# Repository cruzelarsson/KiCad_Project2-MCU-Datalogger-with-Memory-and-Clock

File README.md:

MCU Datalogger with memory and clock 

• Designed and debugged multi-layer PCB design using microcontroller, EEPROM, and RTC module with a regulated power supply, improving thermal performance ~30% by utilizing accurate design & routing methodologies ensuring zero DRC & ERC errors.

• Evaluated electrical and firmware-level interactions between MCU and peripherals for stable operation.

• Validated MCU communication protocols using I2C for peripheral data exchange.

•	Produced a compact design with status LEDs, mounting holes and modular connectors, ensuring physical durability and visible feedback. 

-------------------------------------------------------------------------------------------------------------------------------------------------------
This project — MCU Datalogger with Memory and Clock — was supported by PCBWay through their PCB prototyping sponsorship program.

PCBWay provided high-quality manufactured boards that arrived perfectly aligned and finished. The fabrication quality was excellent, with sharp silkscreen printing, clean solder masks, and precise drill accuracy.

A huge thanks to PCBWay for their support in helping bring this project to life. Their fast turnaround and reliable service made the prototyping process straightforward and efficient.

Below you will find the printed out board; the missing components will be added and uploaded soon. Thank you!

-------------------------------------------------------------------------------------------------------------------------------------------------------
3D layout of 2 layer PCB (final design)

-------------------------------------------------------------------------------------------------------------------------------------------------------

PCB Board layout with board specifications 

-------------------------------------------------------------------------------------------------------------------------------------------------------

Schematic Editor Layout of MCU Datalogger

-------------------------------------------------------------------------------------------------------------------------------------------------------

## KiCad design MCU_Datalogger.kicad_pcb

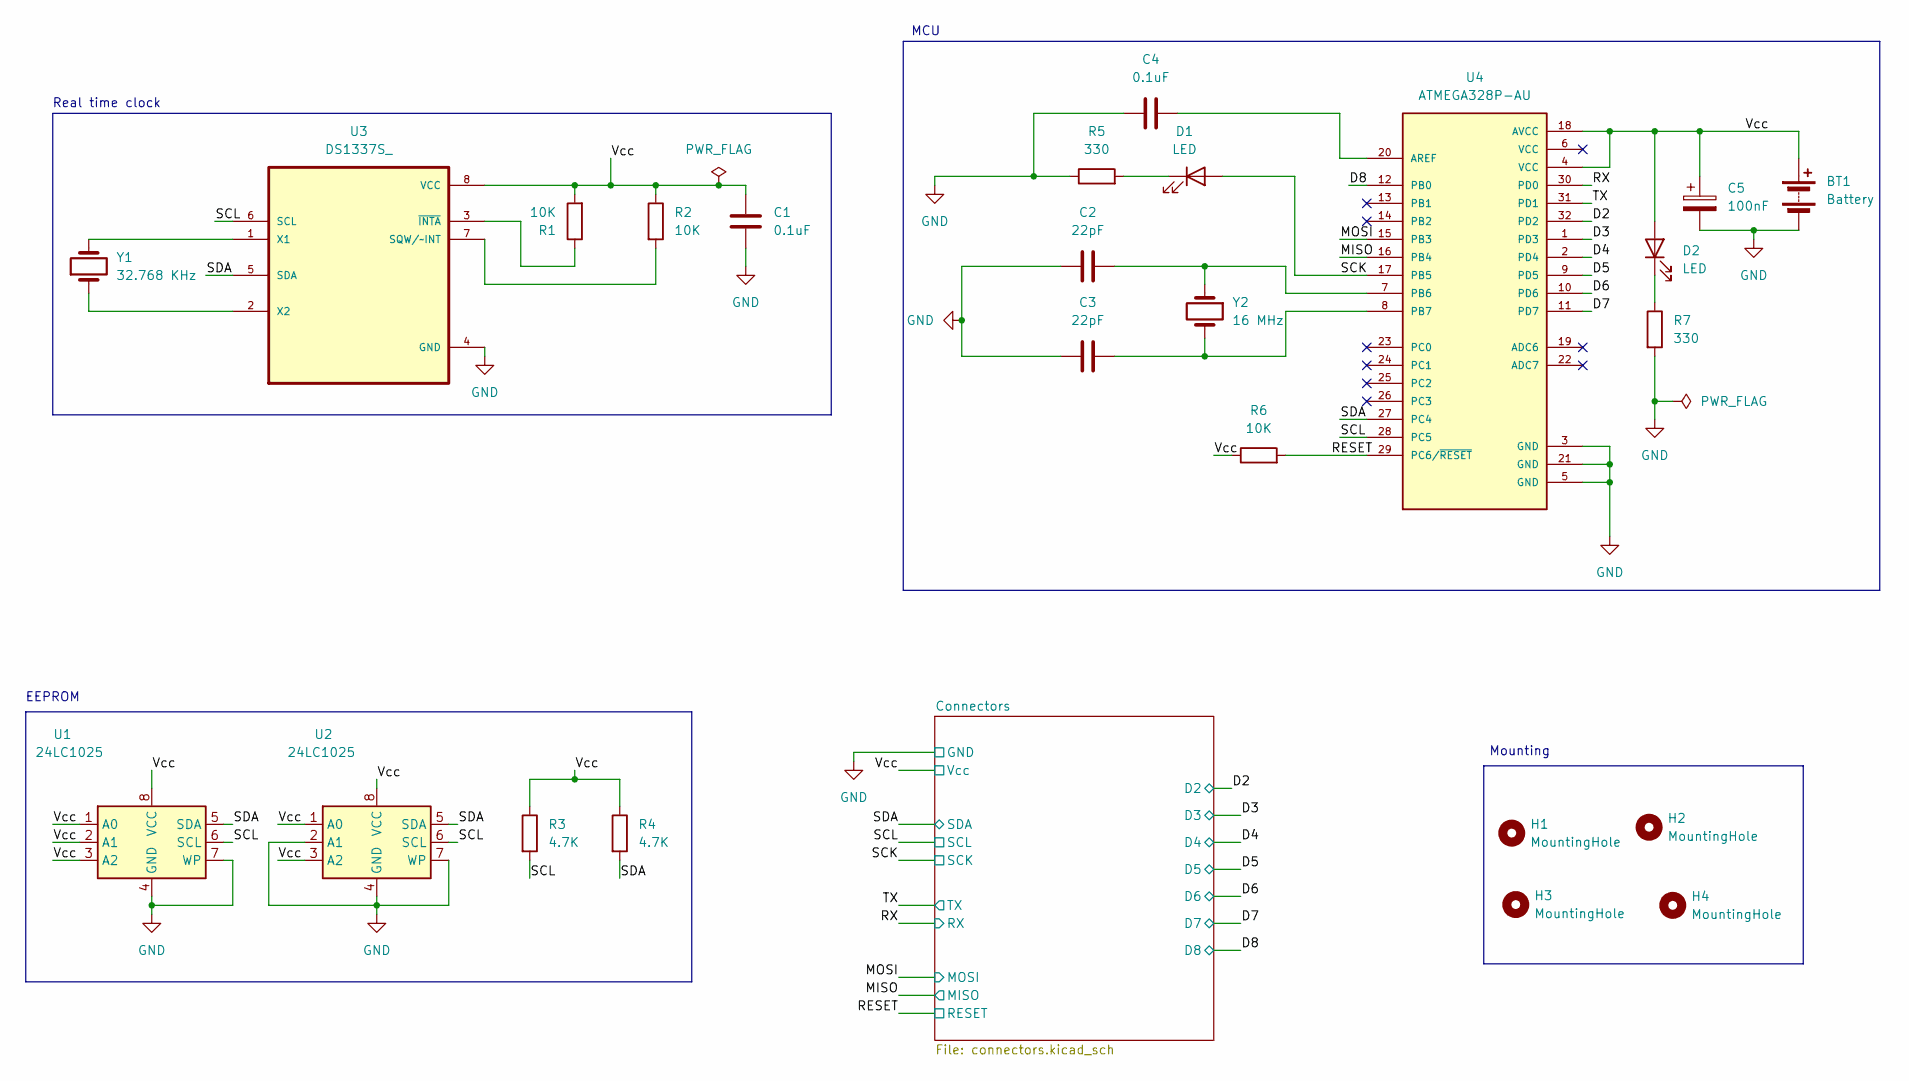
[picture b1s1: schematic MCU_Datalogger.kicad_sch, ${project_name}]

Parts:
BT1: Battery; PinHeader_1x02_P2.54mm_Vertical
C1, C4: 0.1uF; C_0805_2012Metric
C2, C3: 22pF; C_0805_2012Metric
C5: 100nF; C_0805_2012Metric
D1, D2: LED; LED_0805_2012Metric
H1, H2, H3, H4: MountingHole; MountingHole_2.1mm
R1, R2, R6: 10K; R_0805_2012Metric
R3, R4: 4.7K; R_0805_2012Metric
R5, R7: 330; R_0805_2012Metric
U1, U2: 24LC1025; SOIC-8_5.3x5.3mm_P1.27mm
U3: DS1337S_; SOIC127P600X175-8N
U4: ATMEGA328P-AU; QFP80P900X900X120-32N; PARTREV 8271A
Y1: 32.768 KHz; Crystal_SMD_5032-2Pin_5.0x3.2mm_HandSoldering
Y2: 16 MHz; Crystal_SMD_5032-2Pin_5.0x3.2mm_HandSoldering

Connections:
/D2: U4.32 (PD2); also elsewhere on the board
/D3: U4.1 (PD3); also elsewhere on the board
/D4: U4.2 (PD4); also elsewhere on the board
/D5: U4.9 (PD5); also elsewhere on the board
/D6: U4.10 (PD6); also elsewhere on the board
/D7: U4.11 (PD7); also elsewhere on the board
/D8: U4.12 (PB0); also elsewhere on the board
/MISO: U4.16 (PB4); also elsewhere on the board
/MOSI: U4.15 (PB3); also elsewhere on the board
/RESET: R6.2, U4.29 (PC6/~RESET); also elsewhere on the board
/RX: U4.30 (PD0); also elsewhere on the board
/SCK: D1.2 (A), U4.17 (PB5); also elsewhere on the board
/SCL: R3.2, U1.6 (SCL), U2.6 (SCL), U3.6 (SCL), U4.28 (PC5); also elsewhere on the board
/SDA: R4.2, U1.5 (SDA), U2.5 (SDA), U3.5 (SDA), U4.27 (PC4); also elsewhere on the board
/TX: U4.31 (PD1); also elsewhere on the board
/Vcc: BT1.1 (+), C1.1, C5.1, D2.2 (A), R1.2, R2.1, R3.1, R4.1, R6.1, U1.1 (A0), U1.2 (A1), U1.3 (A2), U1.8 (VCC), U2.1 (A0), U2.3 (A2), U2.8 (VCC), U3.8 (VCC), U4.4 (VCC), U4.18 (AVCC); also elsewhere on the board
GND: BT1.2 (-), C1.2, C2.1, C3.1, C4.1, C5.2, R5.1, R7.2, U1.4 (GND), U1.7 (WP), U2.2 (A1), U2.4 (GND), U2.7 (WP), U3.4 (GND), U4.3 (GND), U4.5 (GND), U4.21 (GND); also elsewhere on the board
unnamed: D1.1 (K), R5.2
unnamed: D2.1 (K), R7.1
unnamed: R2.2, U3.7 (SQW/~INT)
unnamed: U3.1 (X1), Y1.2
unnamed: U3.2 (X2), Y1.1
unnamed: R1.1, U3.3 (~INTA)
unnamed: C4.2, U4.20 (AREF)
unnamed: C2.2, U4.7 (PB6), Y2.1
unnamed: C3.2, U4.8 (PB7), Y2.2

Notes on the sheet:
Mounting
Real time clock
MCU
EEPROM

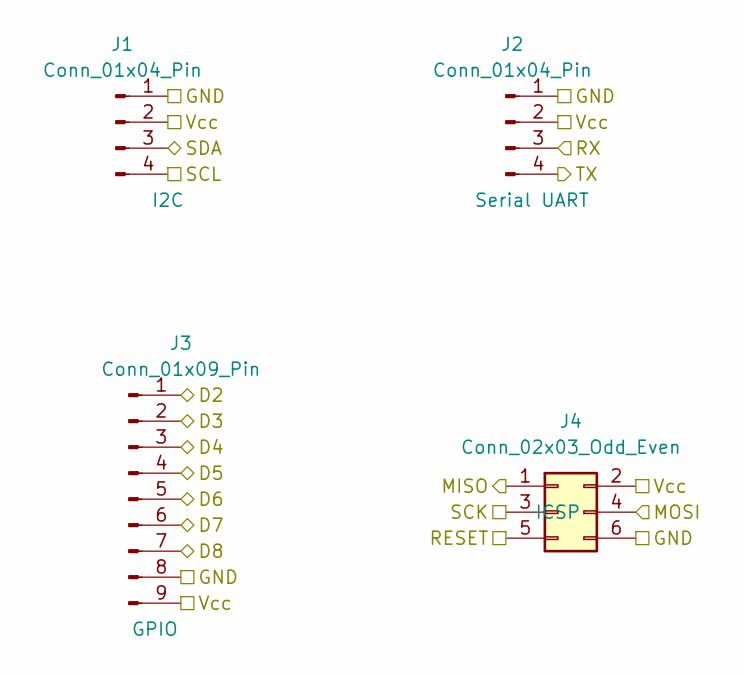
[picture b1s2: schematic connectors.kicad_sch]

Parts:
J1, J2: Conn_01x04_Pin; PinHeader_1x04_P2.54mm_Vertical
J3: Conn_01x09_Pin; PinHeader_1x09_P2.54mm_Vertical
J4: Conn_02x03_Odd_Even; PinHeader_2x03_P2.54mm_Vertical

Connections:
/D2: J3.1; also elsewhere on the board
/D3: J3.2; also elsewhere on the board
/D4: J3.3; also elsewhere on the board
/D5: J3.4; also elsewhere on the board
/D6: J3.5; also elsewhere on the board
/D7: J3.6; also elsewhere on the board
/D8: J3.7; also elsewhere on the board
/MISO: J4.1; also elsewhere on the board
/MOSI: J4.4; also elsewhere on the board
/RESET: J4.5; also elsewhere on the board
/RX: J2.3; also elsewhere on the board
/SCK: J4.3; also elsewhere on the board
/SCL: J1.4; also elsewhere on the board
/SDA: J1.3; also elsewhere on the board
/TX: J2.4; also elsewhere on the board
/Vcc: J1.2, J2.2, J3.9, J4.2; also elsewhere on the board
GND: J1.1, J2.1, J3.8, J4.6; also elsewhere on the board

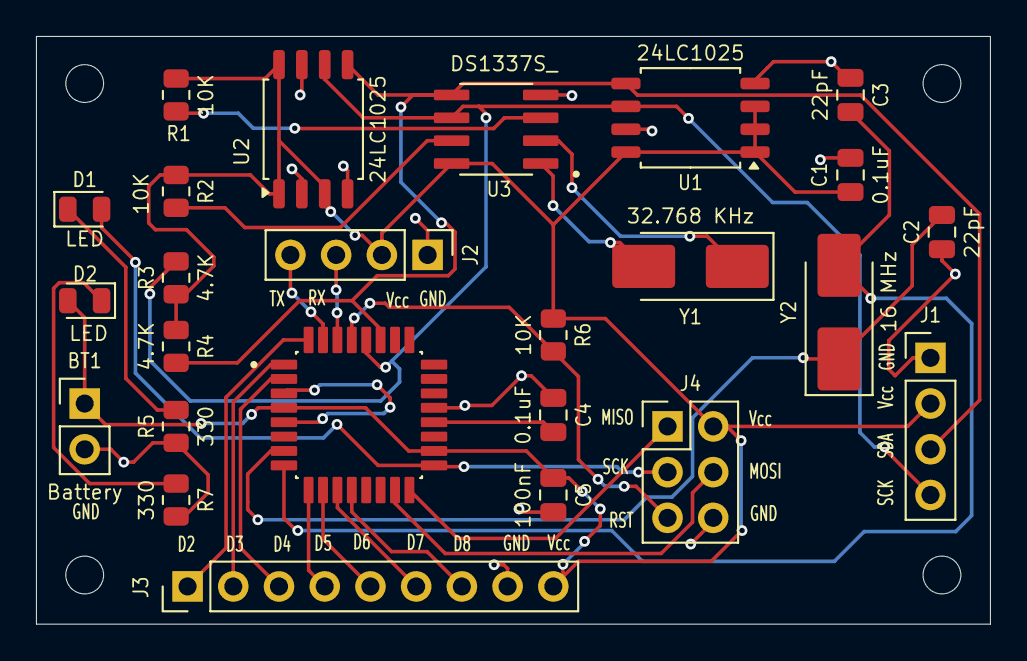
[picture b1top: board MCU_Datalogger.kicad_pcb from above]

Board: 2 copper layers, 53.0 x 32.6 mm, 29 parts (0 on the bottom side), 26 nets.

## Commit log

2025-08-30 First commit of New Project
2025-08-30 Setup of EEschema for new project
2025-08-30 Added the required symbols for the Project to the added schematics sheets
2025-08-30 Saving changes
2025-08-30 Change in component placements
2025-08-30 Assigned footprints to components
2025-08-30 Added wiring to main sheet
2025-08-30 Completed wiring of second sheet + added connectection between the 2 sheets
2025-08-30 Added comments and made the schematics neat
2025-08-30 Completed placements of footprints
2025-08-31 Added proper Routing plus GND
2025-08-31 Fixed various errors and made the PCB more redeable
2025-08-31 Added silkscreens and labels
2025-08-31 Fixed 2 bugs in the Schematics diagram
2025-08-31 Additional bug fixes with rerouting of Routes
2025-08-31 Check point of Project Completion
2025-08-31 Added missing 3D models [Visual Fix]
2025-08-31 Completion of MCU Data logger 2 layer project
2025-09-20 README.md
